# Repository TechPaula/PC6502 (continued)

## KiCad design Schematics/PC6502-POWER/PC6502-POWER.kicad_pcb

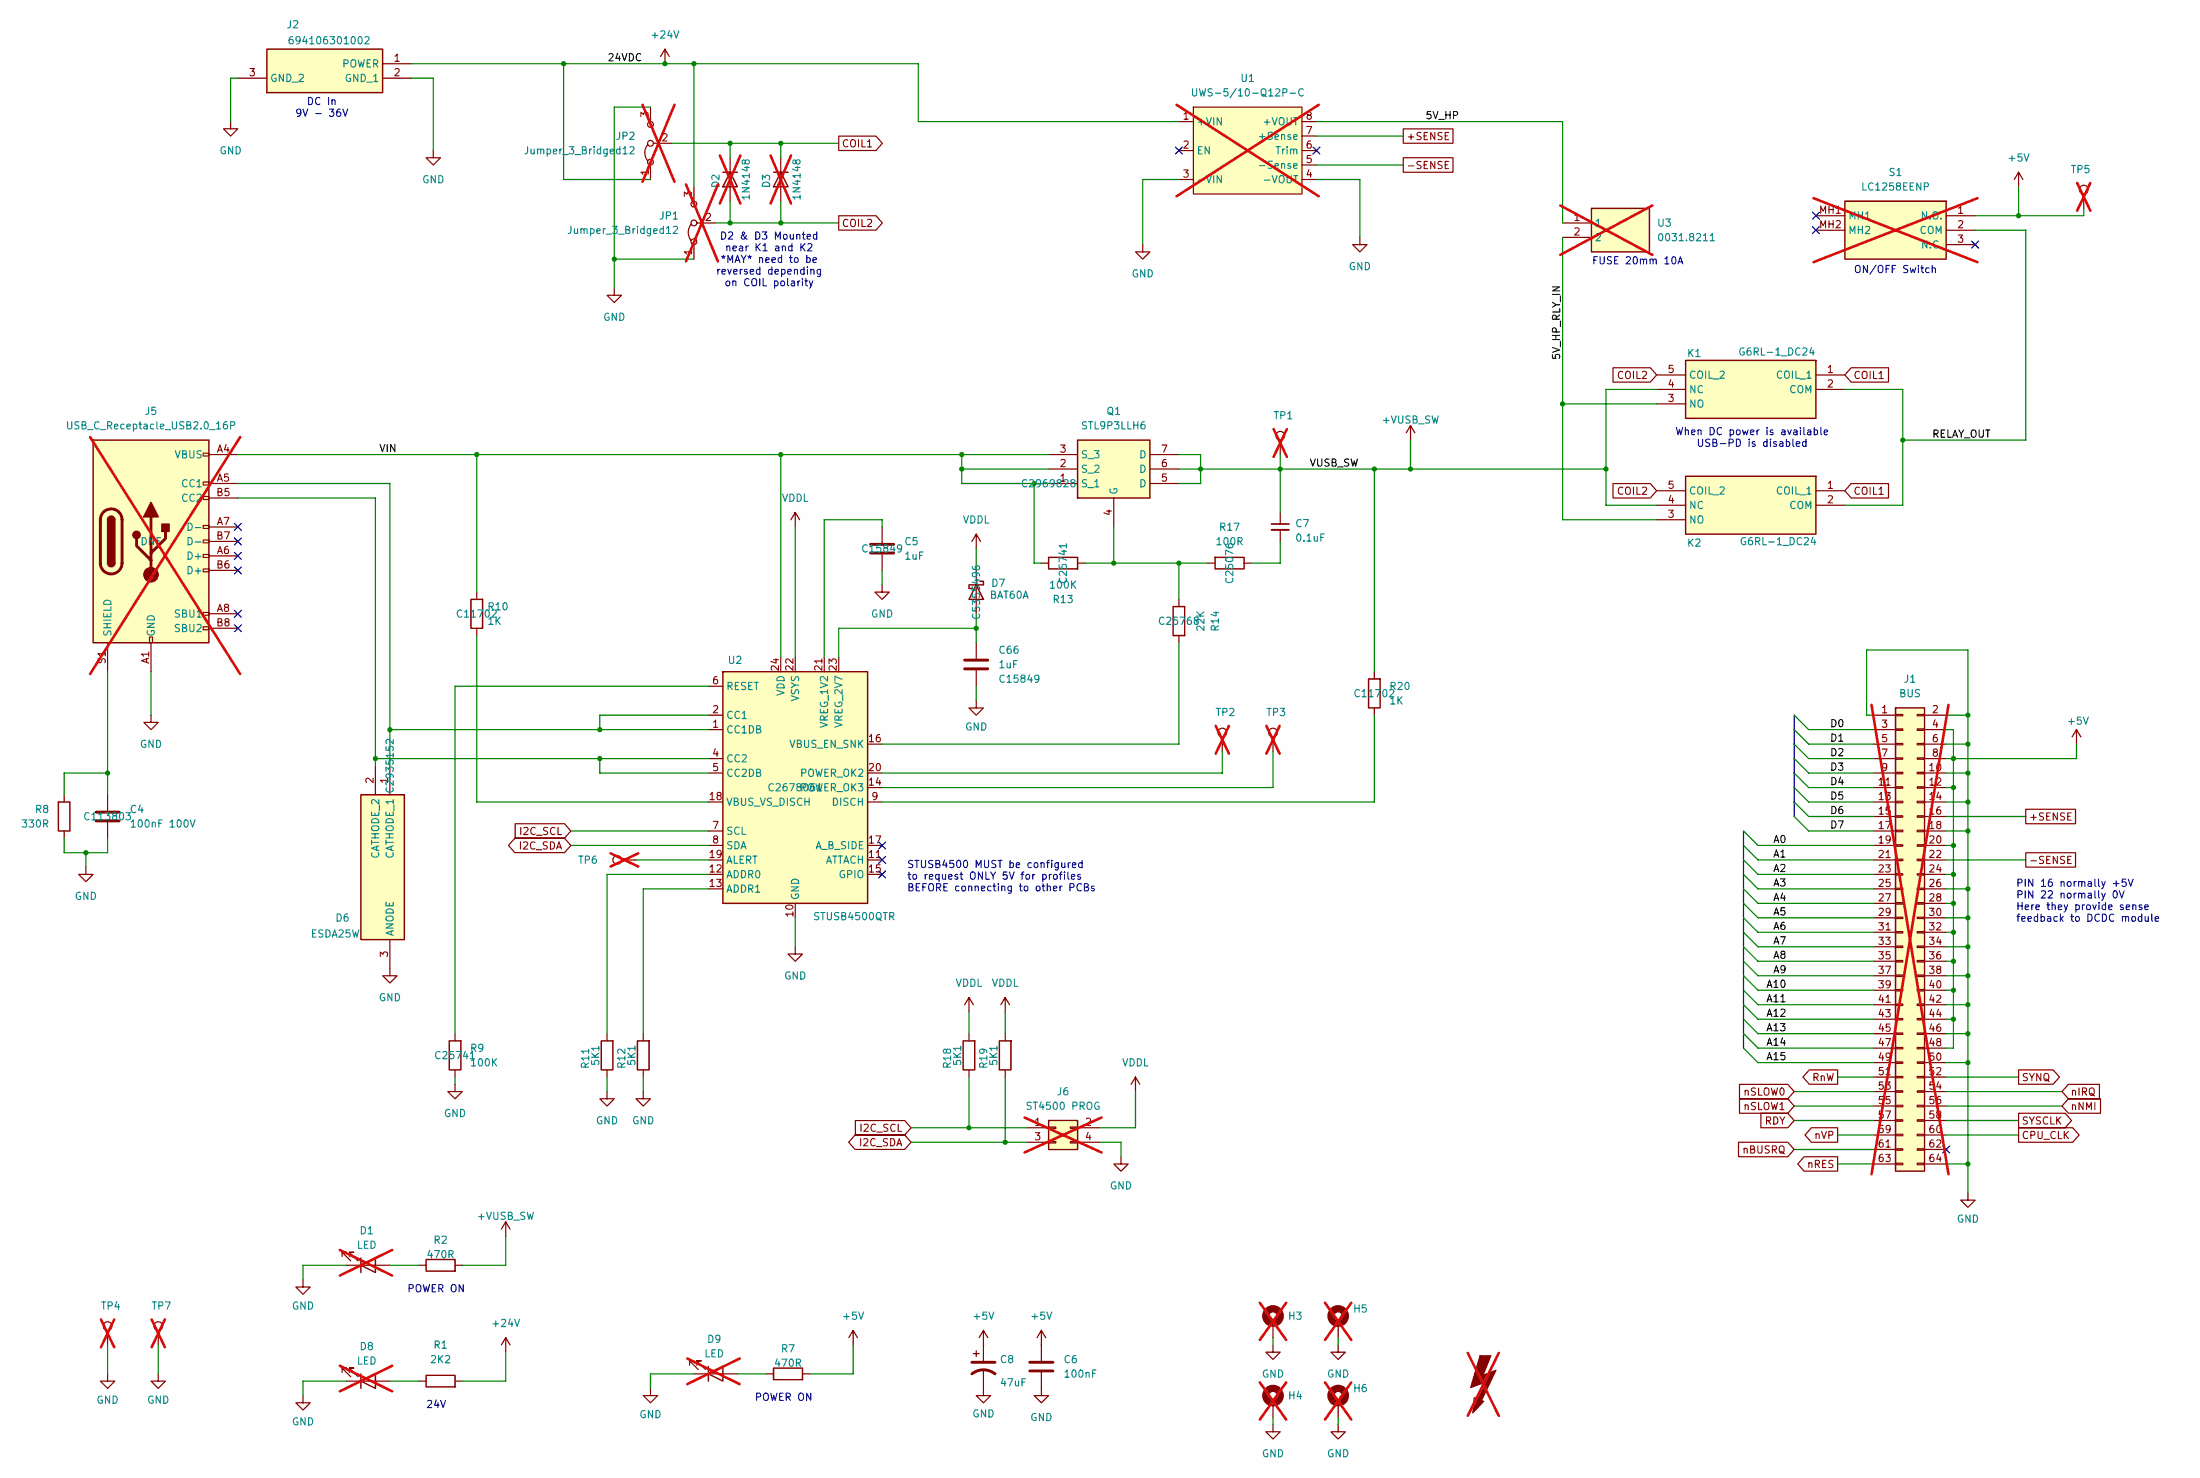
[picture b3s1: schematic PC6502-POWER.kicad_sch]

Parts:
C4: 100nF 100V; C_0603_1608Metric; LCSC C113803
C5, C66: 1uF; C_0603_1608Metric; LCSC C15849
C6: 100nF; C_0805_2012Metric; LCSC C49678
C7: 0.1uF; C_0603_1608Metric; LCSC C113803
C8: 47uF; C_1206_3216Metric; LCSC C96123
D1, D8, D9: LED; LTL4221NHBP; LCSC DNF; not fitted
D2, D3: 1N4148; D_DO-35_SOD27_P7.62mm_Horizontal; LCSC DNF; not fitted
D6: ESDA25W; SOT65P210X110-3N; Mouser Part Number 511-ESDA25W
D7: BAT60A; D_SOD-323; LCSC C5355496
FOX1: SYM_Flash_Large; Fox_avatar_18mm; LCSC DNF; not fitted
H3, H4, H5, H6: MountingHole_Pad; MountingHole_3.2mm_M3_Pad_TopBottom; LCSC DNF; not fitted
J1: BUS; PinSocket_2x32_P2.54mm_Vertical; LCSC DNF; not fitted
J2: 694106301002; 694106301002_1; Mouser Part Number 710-694106301002
J5: USB_C_Receptacle_USB2.0_16P; USB_C_Receptacle_HCTL_HC-TYPE-C-16P-01A; LCSC DNF; not fitted
J6: ST4500 PROG; PinHeader_2x02_P2.54mm_Horizontal; LCSC DNF; not fitted
JP1, JP2: Jumper_3_Bridged12; SolderJumper-3_P1.3mm_Bridged12_RoundedPad1.0x1.5mm_NumberL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; LCSC DNF; not fitted
K1, K2: G6RL-1_DC24; G6RL1DC24; Mouser Part Number 653-G6RL-1-DC24
Q1: STL9P3LLH6; STL20N6F7; Manufacturer_Part_Number STL9P3LLH6; Mouser Part Number 511-STL9P3LLH6
R1: 2K2; R_0603_1608Metric_Pad0.98x0.95mm_HandSolder; LCSC C4190
R2, R7: 470R; R_0603_1608Metric_Pad0.98x0.95mm_HandSolder; LCSC C23179
R8: 330R; R_0402_1005Metric; LCSC C25104
R9, R13: 100K; R_0402_1005Metric; LCSC C25741
R10, R20: 1K; R_0402_1005Metric; LCSC C11702
R11, R12, R18, R19: 5K1; R_0402_1005Metric; LCSC C25905
R14: 22K; R_0402_1005Metric; LCSC C25768
R17: 100R; R_0402_1005Metric; LCSC C25076
S1: LC1258EENP; Mouser Part Number 612-LC1258EENP; not fitted
TP1, TP2, TP3, TP4, TP5, TP6, TP7: TestPoint; TestPoint_Loop_D1.80mm_Drill1.0mm_Beaded; LCSC DNF; not fitted
U1: UWS-5/10-Q12P-C; UWS510Q48PC; LCSC DNF; not fitted
U2: STUSB4500QTR; QFN-24-1EP_4x4mm_P0.5mm_EP2.7x2.7mm; LCSC C2678061
U3: 0031.8211; 00318211; Mouser Part Number 693-0031.8211; not fitted

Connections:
+5V: C6.1, C8.1, J1.4, J1.8, J1.12, J1.20, J1.24, J1.28, J1.32, J1.36, J1.40, J1.44, J1.48, R7.2, S1.1 (N.O.), TP5.1
+24V: J2.1 (POWER), JP1.3 (B), JP2.1 (A), R1.2, U1.1 (+VIN)
+SENSE: J1.16, U1.7 (+Sense)
+VUSB_SW: C7.1, K1.4 (NC), K2.4 (NC), Q1.5 (D), Q1.6 (D), Q1.7 (D), R2.2, R20.2, TP1.1
-SENSE: J1.22, U1.5 (-Sense)
/5V_HP: U1.8 (+VOUT), U3.1
/5V_HP_RLY_IN: K1.3 (NO), K2.3 (NO), U3.2
/A0: J1.19
/A1: J1.21
/A2: J1.23
/A3: J1.25
/A4: J1.27
/A5: J1.29
/A6: J1.31
/A7: J1.33
/A8: J1.35
/A9: J1.37
/A10: J1.39
/A11: J1.41
/A12: J1.43
/A13: J1.45
/A14: J1.47
/A15: J1.49
/D0: J1.3
/D1: J1.5
/D2: J1.7
/D3: J1.9
/D4: J1.11
/D5: J1.13
/D6: J1.15
/D7: J1.17
/RELAY_OUT: K1.2 (COM), K2.2 (COM), S1.2 (COM)
/VIN: J5.A4 (VBUS), J5.A9 (VBUS), J5.B4 (VBUS), J5.B9 (VBUS), Q1.1 (S_1), Q1.2 (S_2), Q1.3 (S_3), R10.2, R13.1, U2.24 (VDD)
COIL1: D2.1 (K), D3.1 (K), JP2.2 (C), K1.1 (COIL_1), K2.1 (COIL_1)
COIL2: D2.2 (A), D3.2 (A), JP1.2 (C), K1.5 (COIL_2), K2.5 (COIL_2)
CPU_CLK: J1.60
GND: C4.2, C5.2, C6.2, C8.2, C66.2, D1.1 (K), D6.3 (ANODE), D8.1 (K), D9.1 (K), H3.1, H4.1, H5.1, H6.1, J1.1, J1.2, J1.6, J1.10, J1.14, J1.18, J1.26, J1.30, J1.34, J1.38, J1.42, J1.46, J1.50, J1.64, J2.2 (GND_1), J2.3 (GND_2), J5.A1 (GND), J5.A12 (GND), J5.B1 (GND), J5.B12 (GND), J6.4, JP1.1 (A), JP2.3 (B), R8.1, R9.1, R11.1, R12.1, TP4.1, TP7.1, U1.3 (-VIN), U1.4 (-VOUT), U2.10 (GND), U2.25 (GND)
I2C_SCL: J6.1, R18.1, U2.7 (SCL)
I2C_SDA: J6.3, R19.1, U2.8 (SDA)
unnamed: C7.2, R17.1
unnamed: D1.2 (A), R2.1
unnamed: D6.1 (CATHODE_1), J5.A5 (CC1), U2.1 (CC1DB), U2.2 (CC1)
unnamed: D6.2 (CATHODE_2), J5.B5 (CC2), U2.4 (CC2), U2.5 (CC2DB)
unnamed: C66.1, D7.2 (A), U2.23 (VREG_2V7)
unnamed: D8.2 (A), R1.1
unnamed: D9.2 (A), R7.1
unnamed: C4.1, J5.S1 (SHIELD), R8.2
unnamed: Q1.4 (G), R13.2, R14.1, R17.2
unnamed: R11.2, U2.12 (ADDR0)
unnamed: R12.2, U2.13 (ADDR1)
unnamed: TP6.1, U2.19 (ALERT)
unnamed: R20.1, U2.9 (DISCH)
unnamed: TP2.1, U2.20 (POWER_OK2)
unnamed: TP3.1, U2.14 (POWER_OK3)
unnamed: R9.2, U2.6 (RESET)
unnamed: R14.2, U2.16 (VBUS_EN_SNK)
unnamed: R10.1, U2.18 (VBUS_VS_DISCH)
unnamed: C5.1, U2.21 (VREG_1V2)
RDY: J1.57
RnW: J1.51
SYNQ: J1.52
SYSCLK: J1.58
VDDL: D7.1 (K), J6.2, R18.2, R19.2, U2.22 (VSYS)
nBUSRQ: J1.61
nIRQ: J1.54
nNMI: J1.56
nRES: J1.63
nSLOW0: J1.53
nSLOW1: J1.55
nVP: J1.59

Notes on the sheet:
D2 & D3 Mounted near K1 and K2 *MAY* need to be reversed depending on COIL polarity
PIN 16 normally +5V PIN 22 normally 0V Here they provide sense feedback to DCDC module
POWER ON
DC In 9V - 36V
ON/OFF Switch
24V
When DC power is available USB-PD is disabled
STUSB4500 MUST be configured to request ONLY 5V for profiles BEFORE connecting to other PCBs
FUSE 20mm 10A

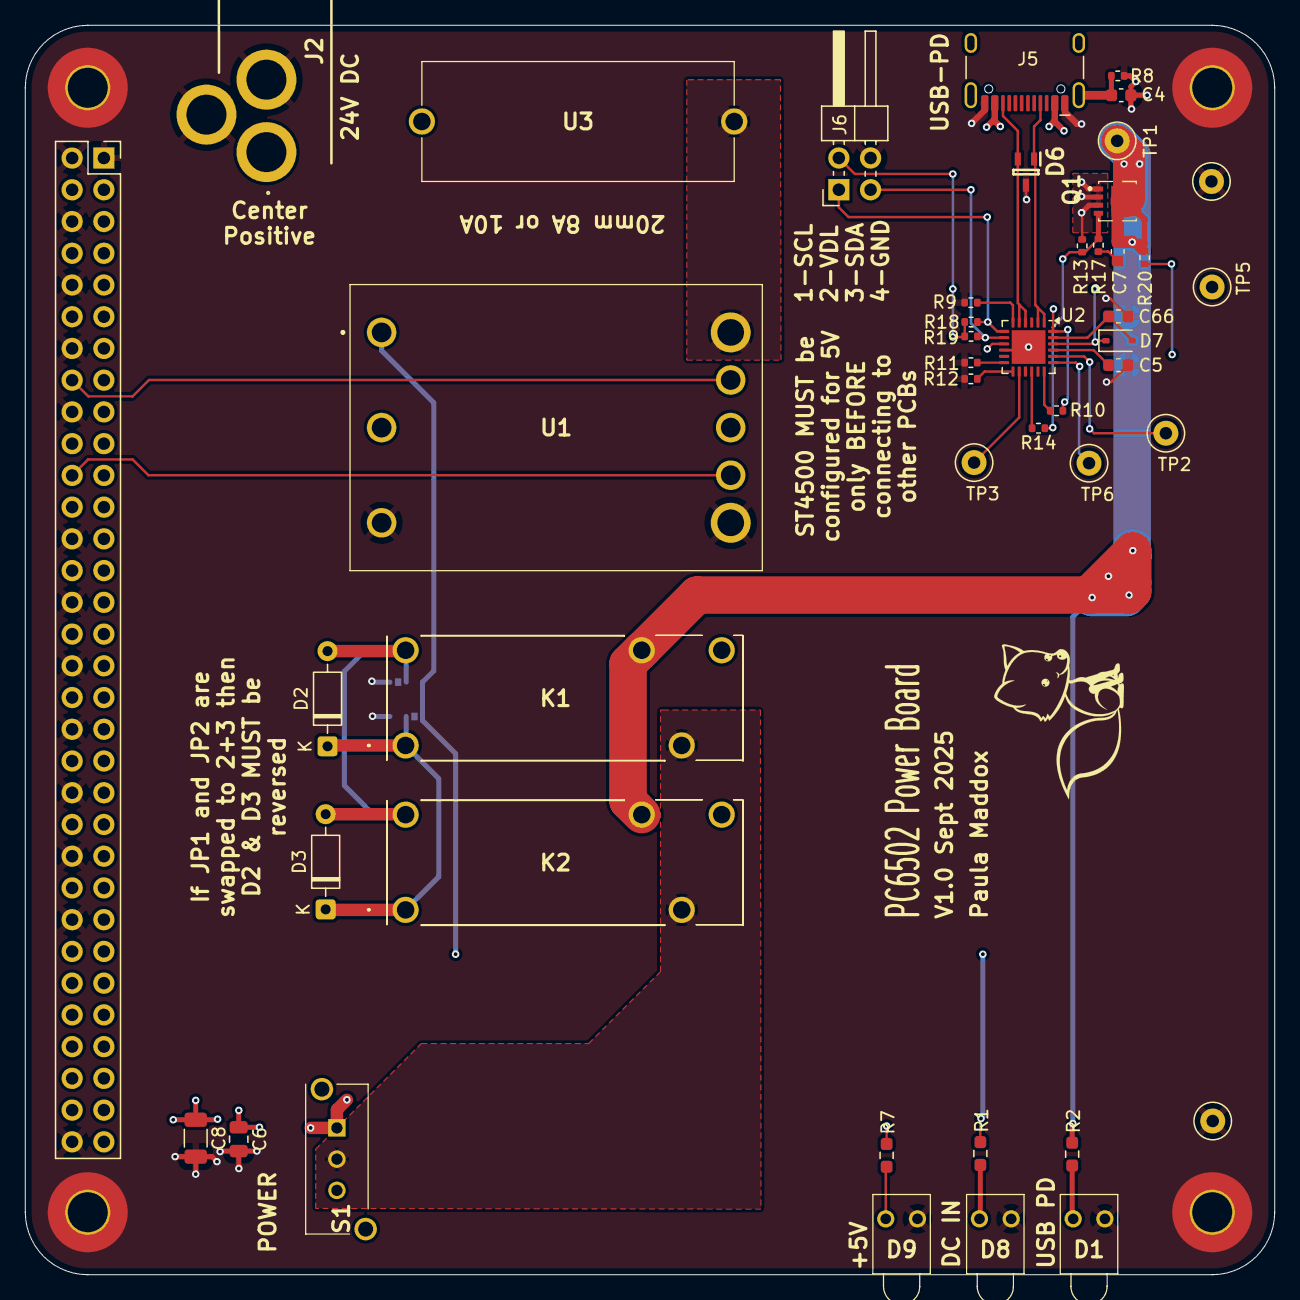
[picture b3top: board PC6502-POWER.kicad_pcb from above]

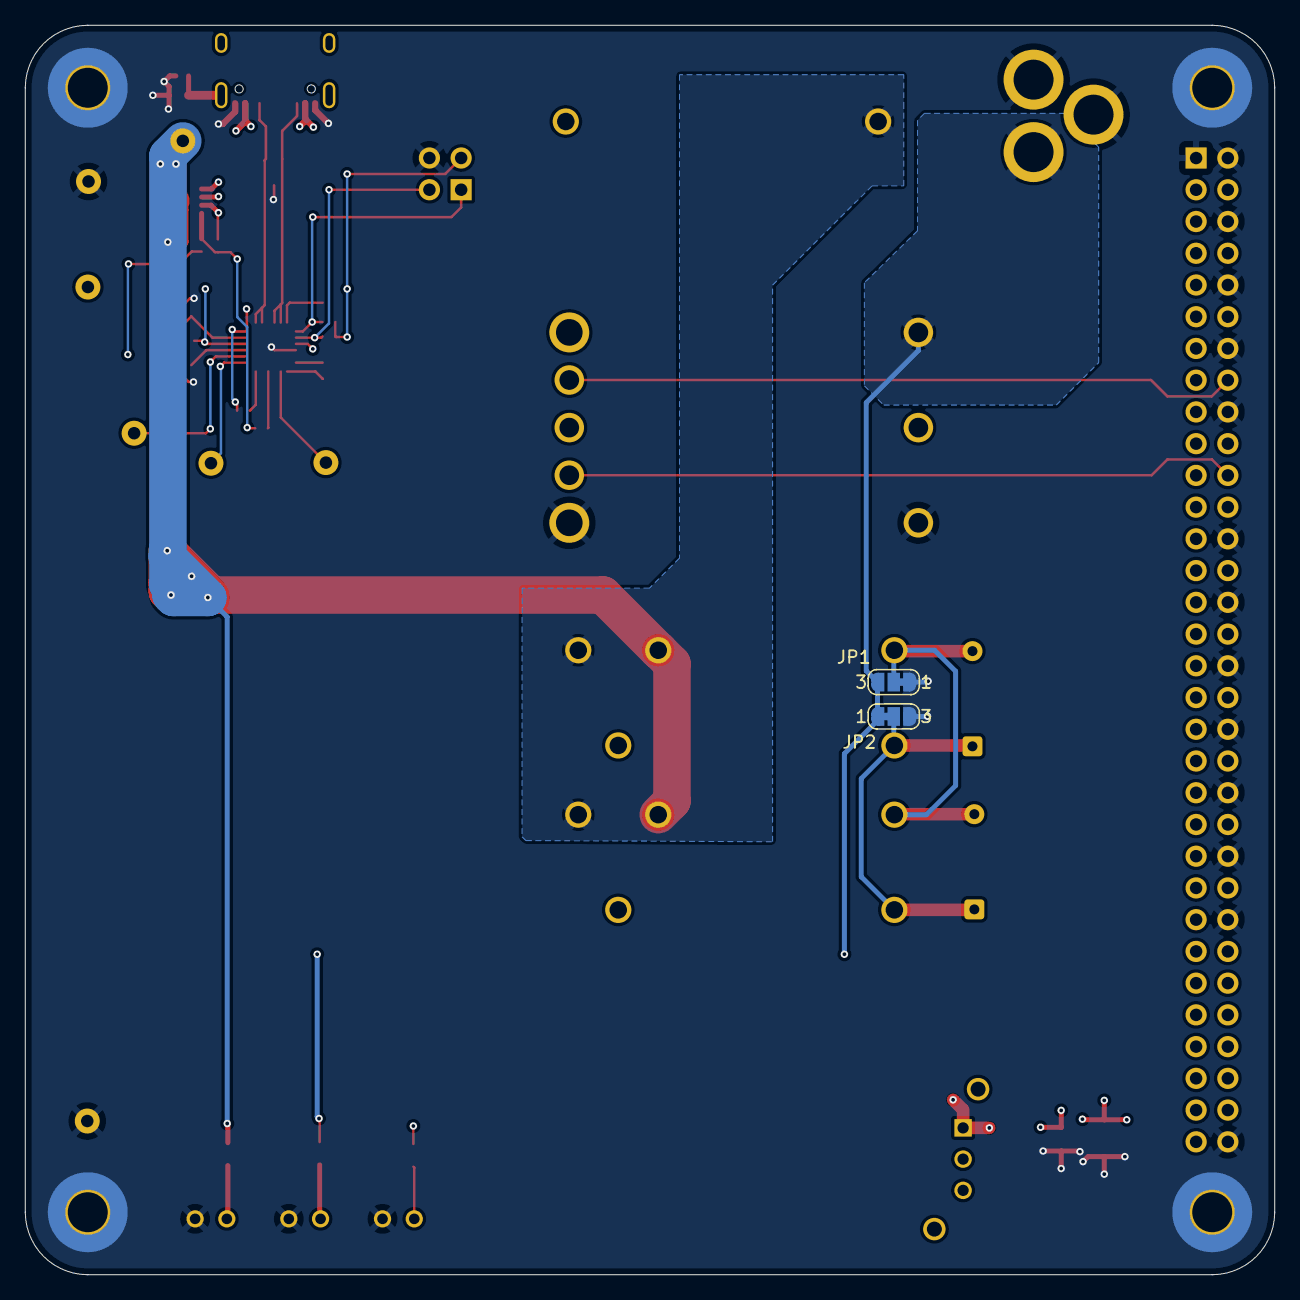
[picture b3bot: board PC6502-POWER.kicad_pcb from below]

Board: 4 copper layers, 100.0 x 100.0 mm, 52 parts (2 on the bottom side), 34 nets.

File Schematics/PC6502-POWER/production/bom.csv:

Designator,Footprint,Quantity,Value,LCSC Part #
C4,0603,1,100nF 100V,C113803
"C5, C66",0603,2,1uF,C15849
C6,0805,1,100nF,C49678
C7,0603,1,0.1uF,C113803
C8,1206,1,47uF,C96123
D6,SOT65P210X110-3N,1,ESDA25W,C2935152
D7,D_SOD-323,1,BAT60A,C5355496
J2,694106301002_1,1,694106301002,DNF
"K1, K2",G6RL1DC24,2,G6RL-1_DC24,DNF
Q1,STL20N6F7,1,STL9P3LLH6,C2969828
R1,0603,1,2K2,C4190
"R10, R20",0402,2,1K,C11702
"R11, R12, R18, R19",0402,4,5K1,C25905
"R13, R9",0402,2,100K,C25741
R14,0402,1,22K,C25768
R17,0402,1,100R,C25076
"R2, R7",0603,2,470R,C23179
R8,0402,1,330R,C25104
U2,QFN-24-1EP_4x4mm_P0.5mm_EP2.7x2.7mm,1,STUSB4500QTR,C2678061

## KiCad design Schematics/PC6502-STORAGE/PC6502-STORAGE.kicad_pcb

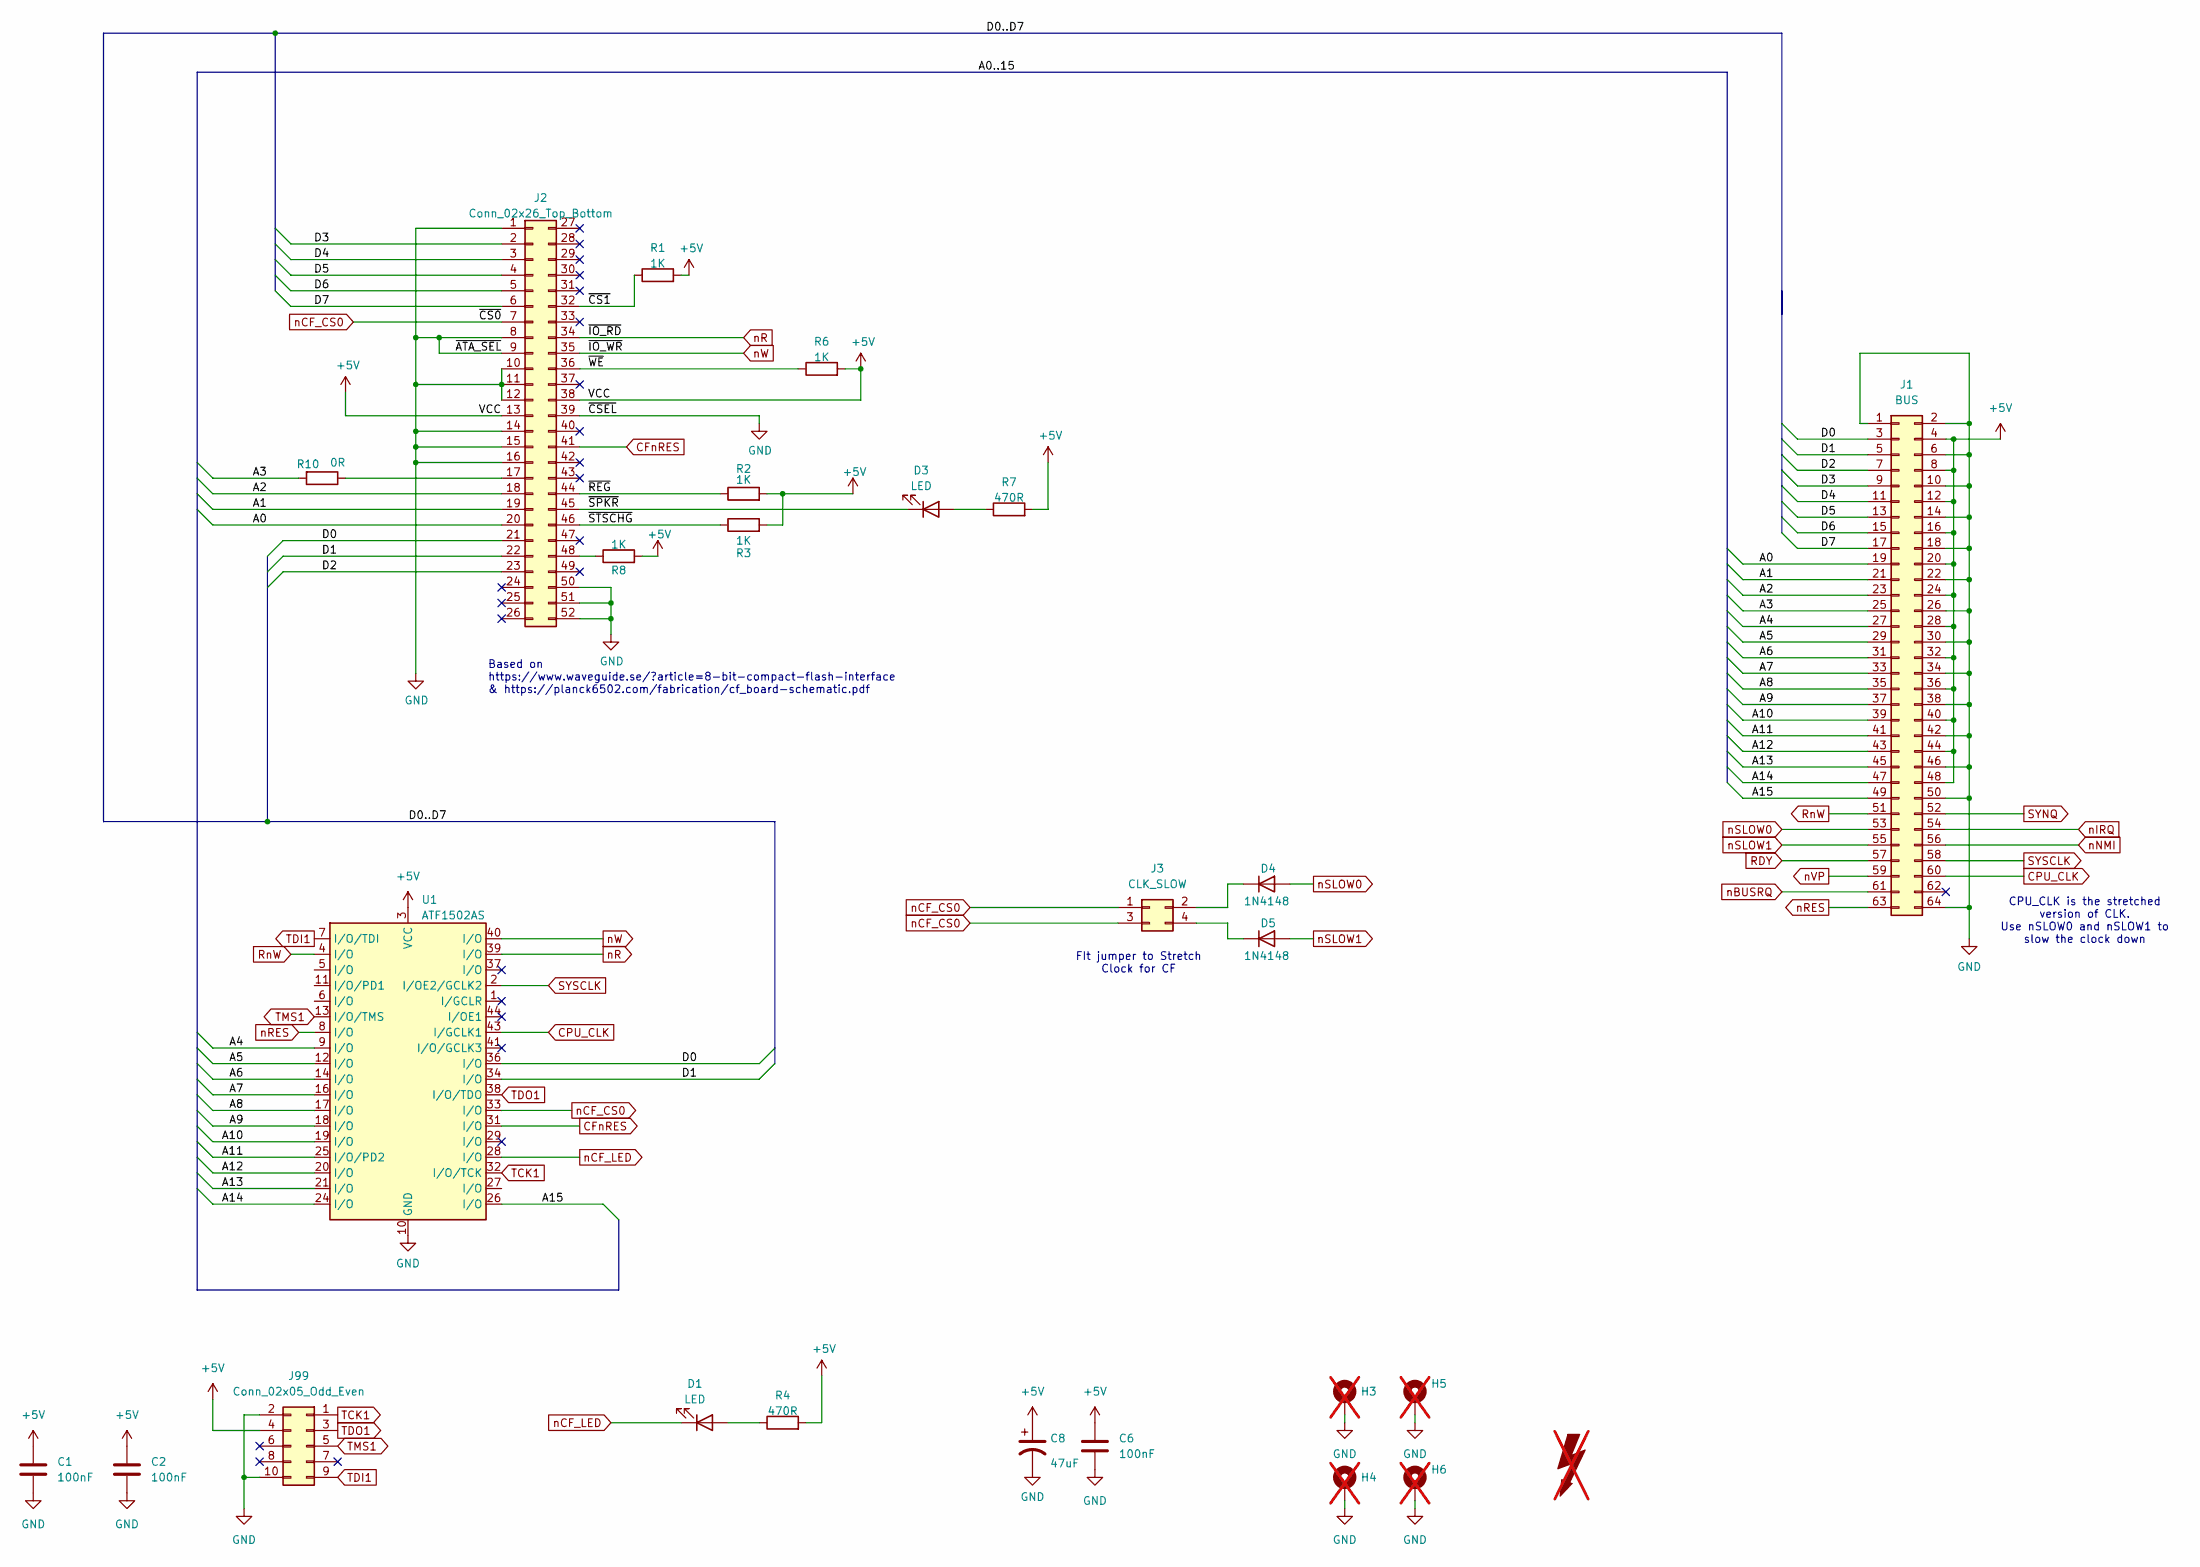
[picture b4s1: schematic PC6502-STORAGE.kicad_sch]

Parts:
C1, C2, C6: 100nF; C_0805_2012Metric
C8: 47uF; C_1206_3216Metric; LCSC C96123
D1, D3: LED; LTL4221NHBP; LCSC DNF
D4, D5: 1N4148; D_DO-35_SOD27_P7.62mm_Horizontal; LCSC DNF
FOX1: SYM_Flash_Large; Fox_avatar_18mm; LCSC DNF; not fitted
H3, H4, H5, H6: MountingHole_Pad; MountingHole_3.2mm_M3_Pad_TopBottom; LCSC DNF; not fitted
J1: BUS; PinSocket_2x32_P2.54mm_Vertical; LCSC DNF
J2: Conn_02x26_Top_Bottom; SD-SMD_CFH-L3C1LBL01MN0; LCSC C444350
J3: CLK_SLOW; PinHeader_2x02_P2.54mm_Horizontal; LCSC DNF
J99: Conn_02x05_Odd_Even; PinHeader_2x05_P2.54mm_Vertical; LCSC DNF
R1, R2, R3, R6, R8: 1K; R_0603_1608Metric_Pad0.98x0.95mm_HandSolder
R4, R7: 470R; R_0603_1608Metric_Pad0.98x0.95mm_HandSolder
R10: 0R; R_0603_1608Metric_Pad0.98x0.95mm_HandSolder
U1: ATF1502AS; PLCC-44_THT-Socket; LCSC DNP

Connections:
+5V: C1.1, C2.1, C6.1, C8.1, J1.4, J1.8, J1.12, J1.16, J1.20, J1.24, J1.28, J1.32, J1.36, J1.40, J1.44, J1.48, J2.13, J2.38, J99.4, R1.2, R2.2, R3.2, R4.2, R6.2, R7.2, R8.2, U1.3 (VCC), U1.15 (VCC), U1.23 (VCC), U1.35 (VCC)
/A0: J1.19, J2.20
/A1: J1.21, J2.19
/A2: J1.23, J2.18
/A3: J1.25, R10.2
/A4: J1.27, U1.9 (I/O)
/A5: J1.29, U1.12 (I/O)
/A6: J1.31, U1.14 (I/O)
/A7: J1.33, U1.16 (I/O)
/A8: J1.35, U1.17 (I/O)
/A9: J1.37, U1.18 (I/O)
/A10: J1.39, U1.19 (I/O)
/A11: J1.41, U1.25 (I/O/PD2)
/A12: J1.43, U1.20 (I/O)
/A13: J1.45, U1.21 (I/O)
/A14: J1.47, U1.24 (I/O)
/A15: J1.49, U1.26 (I/O)
/D0: J1.3, J2.21, U1.36 (I/O)
/D1: J1.5, J2.22, U1.34 (I/O)
/D2: J1.7, J2.23
/D3: J1.9, J2.2
/D4: J1.11, J2.3
/D5: J1.13, J2.4
/D6: J1.15, J2.5
/D7: J1.17, J2.6
/~CS1: J2.32, R1.1
/~REG: J2.44, R2.1
/~SPKR: D3.1 (K), J2.45
/~STSCHG: J2.46, R3.1
/~WE: J2.36, R6.1
CFnRES: J2.41, U1.31 (I/O)
CPU_CLK: J1.60, U1.43 (I/GCLK1)
GND: C1.2, C2.2, C6.2, C8.2, H3.1, H4.1, H5.1, H6.1, J1.1, J1.2, J1.6, J1.10, J1.14, J1.18, J1.22, J1.26, J1.30, J1.34, J1.38, J1.42, J1.46, J1.50, J1.64, J2.1, J2.8, J2.9, J2.10, J2.11, J2.12, J2.14, J2.15, J2.16, J2.39, J2.50, J2.51, J2.52, J99.2, J99.10, U1.10 (GND), U1.22 (GND), U1.30 (GND), U1.42 (GND)
unnamed: D1.2 (A), R4.1
unnamed: D3.2 (A), R7.1
unnamed: D4.1 (K), J3.2
unnamed: D5.1 (K), J3.4
unnamed: J2.17, R10.1
unnamed: J2.48, R8.1
RDY: J1.57
RnW: J1.51, U1.4 (I/O)
SYNQ: J1.52
SYSCLK: J1.58, U1.2 (I/OE2/GCLK2)
TCK1: J99.1, U1.32 (I/O/TCK)
TDI1: J99.9, U1.7 (I/O/TDI)
TDO1: J99.3, U1.38 (I/O/TDO)
TMS1: J99.5, U1.13 (I/O/TMS)
nBUSRQ: J1.61
nCF_CS0: J2.7, J3.1, J3.3, U1.33 (I/O)
nCF_LED: D1.1 (K), U1.28 (I/O)
nIRQ: J1.54
nNMI: J1.56
nR: J2.34, U1.39 (I/O)
nRES: J1.63, U1.8 (I/O)
nSLOW0: D4.2 (A), J1.53
nSLOW1: D5.2 (A), J1.55
nVP: J1.59
nW: J2.35, U1.40 (I/O)

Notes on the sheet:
FIt jumper to Stretch Clock for CF
Based on https://www.waveguide.se/?article=8-bit-compact-flash-interface & https://planck6502.com/fabrication/cf_board-schematic.pdf
CPU_CLK is the stretched version of CLK. Use nSLOW0 and nSLOW1 to slow the clock down

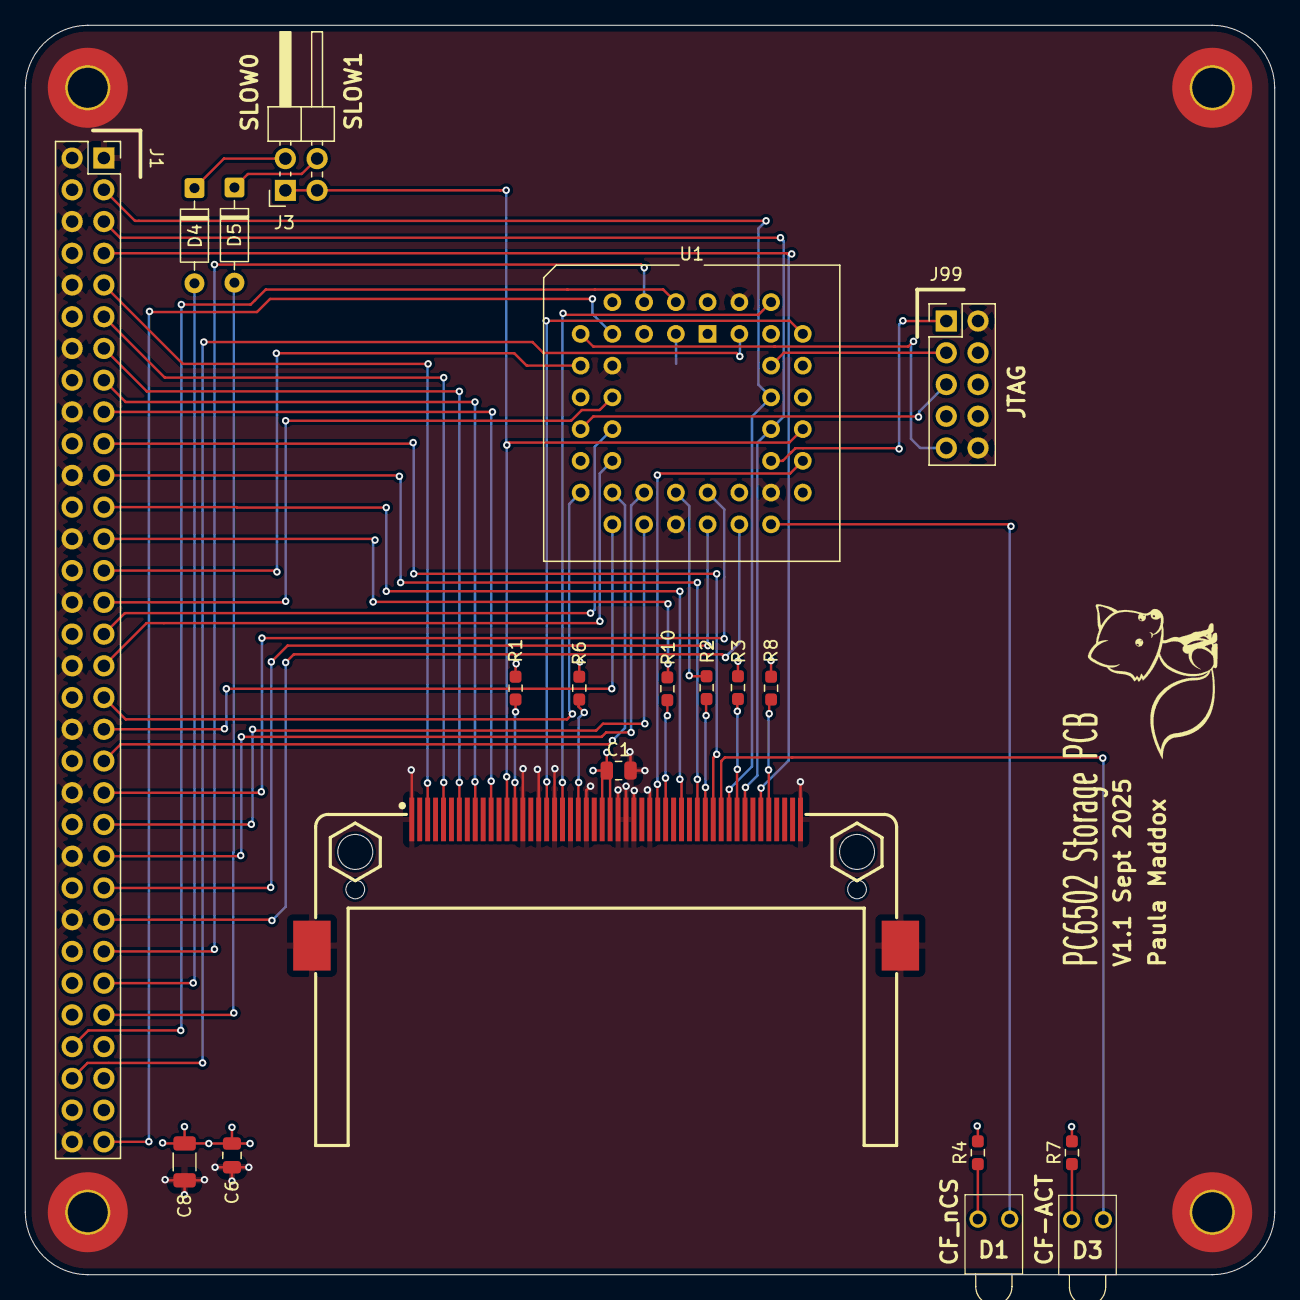
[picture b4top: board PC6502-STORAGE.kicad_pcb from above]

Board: 4 copper layers, 100.0 x 100.0 mm, 26 parts (1 on the bottom side), 52 nets.

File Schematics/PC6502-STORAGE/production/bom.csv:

Designator,Footprint,Quantity,Value,LCSC Part #
"C1, C2, C6",0805,3,100nF,
C8,1206,1,47uF,C96123
"D1, D3",LTL4221NHBP,2,LED,DNF
"D4, D5",D_DO-35_SOD27_P7.62mm_Horizontal,2,1N4148,DNF
J1,PinSocket_2x32_P2.54mm_Vertical,1,BUS,DNF
J2,SD-SMD_CFH-L3C1LBL01MN0,1,Conn_02x26_Top_Bottom,C444350
J3,PinHeader_2x02_P2.54mm_Horizontal,1,CLK_SLOW,DNF
J99,PinHeader_2x05_P2.54mm_Vertical,1,Conn_02x05_Odd_Even,DNF
"R1, R2, R3, R6, R8",0603,5,1K,
R10,0603,1,0R,
"R4, R7",0603,2,470R,
U1,PLCC-44_THT-Socket,1,ATF1502AS,DNP

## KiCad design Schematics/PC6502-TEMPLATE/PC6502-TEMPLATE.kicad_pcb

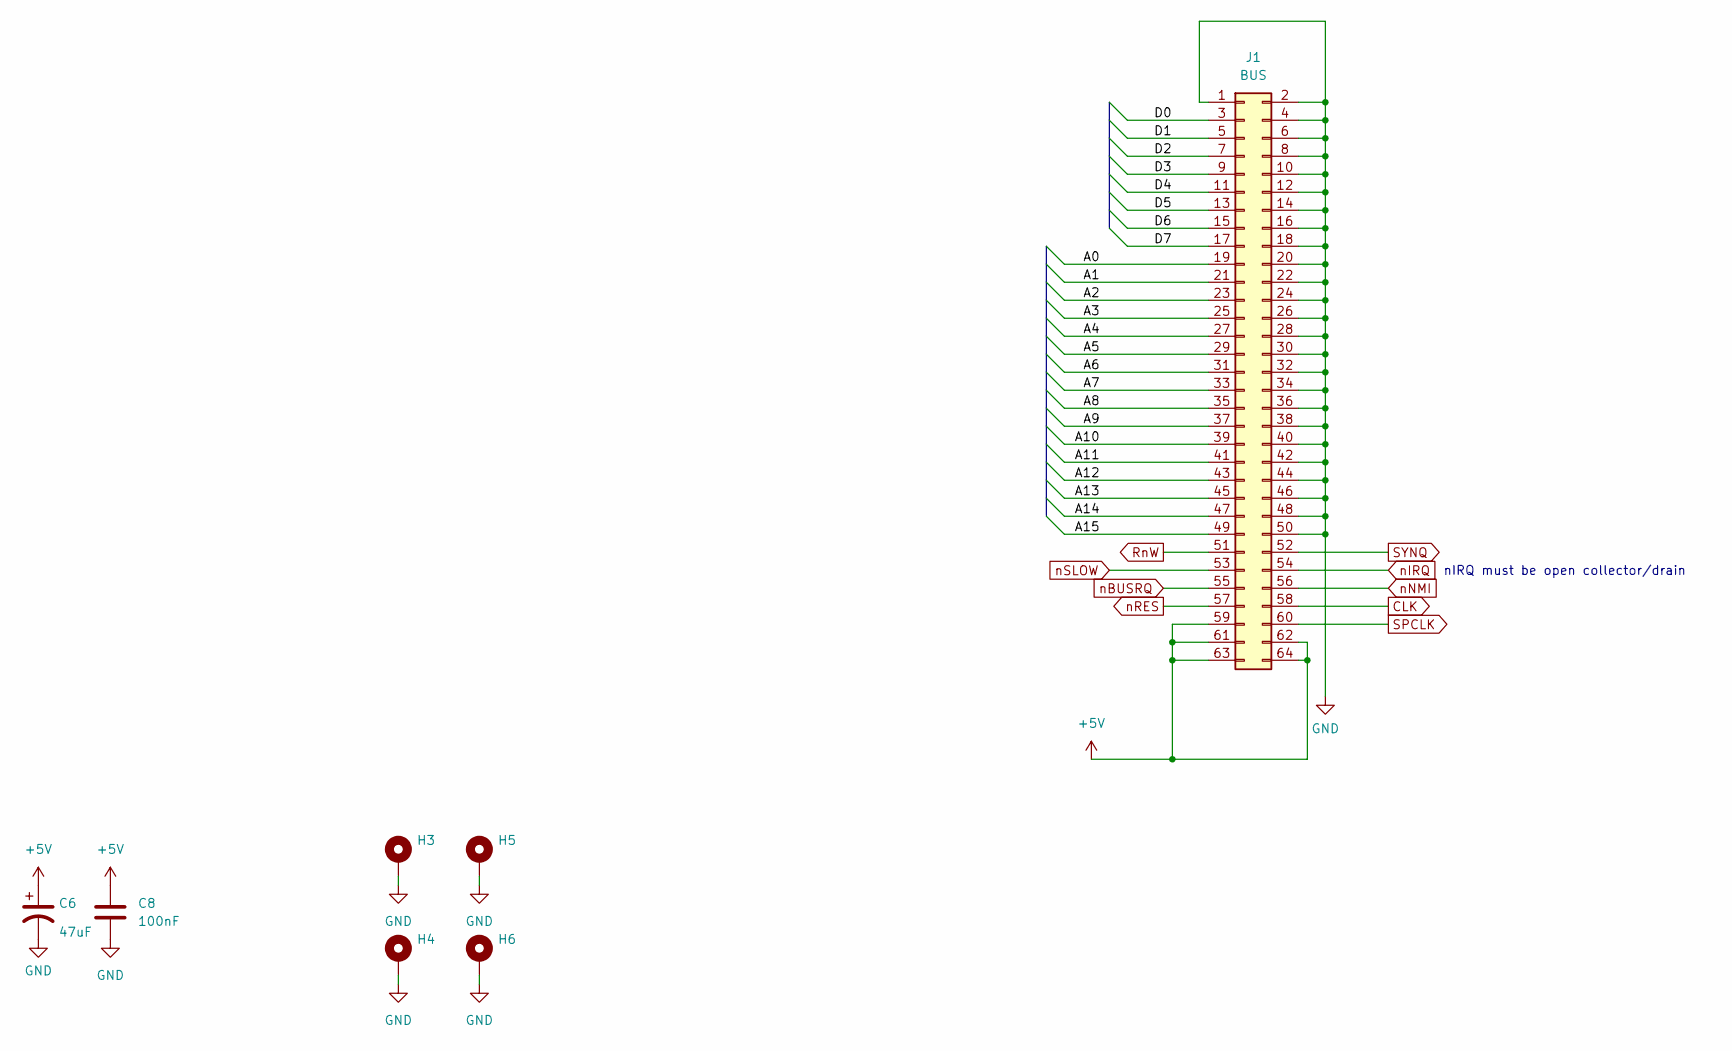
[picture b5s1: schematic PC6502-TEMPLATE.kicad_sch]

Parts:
C6: 47uF; C_1206_3216Metric; LCSC C96123
C8: 100nF; C_0805_2012Metric
H3, H4, H5, H6: MountingHole_Pad; MountingHole_3.2mm_M3_Pad_TopBottom; LCSC DNF
J1: BUS; PinSocket_2x32_P2.54mm_Vertical; LCSC DNF

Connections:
+5V: C6.1, C8.1, J1.59, J1.61, J1.62, J1.63, J1.64
/A0: J1.19
/A1: J1.21
/A2: J1.23
/A3: J1.25
/A4: J1.27
/A5: J1.29
/A6: J1.31
/A7: J1.33
/A8: J1.35
/A9: J1.37
/A10: J1.39
/A11: J1.41
/A12: J1.43
/A13: J1.45
/A14: J1.47
/A15: J1.49
/D0: J1.3
/D1: J1.5
/D2: J1.7
/D3: J1.9
/D4: J1.11
/D5: J1.13
/D6: J1.15
/D7: J1.17
CLK: J1.58
GND: C6.2, C8.2, H3.1, H4.1, H5.1, H6.1, J1.1, J1.2, J1.4, J1.6, J1.8, J1.10, J1.12, J1.14, J1.16, J1.18, J1.20, J1.22, J1.24, J1.26, J1.28, J1.30, J1.32, J1.34, J1.36, J1.38, J1.40, J1.42, J1.44, J1.46, J1.48, J1.50
RnW: J1.51
SPCLK: J1.60
SYNQ: J1.52
nBUSRQ: J1.55
nIRQ: J1.54
nNMI: J1.56
nRES: J1.57
nSLOW: J1.53

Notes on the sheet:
nIRQ must be open collector/drain

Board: 4 copper layers, 7 parts (0 on the bottom side), 2 nets, no tracks yet.
